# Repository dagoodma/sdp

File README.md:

.oo          o                                                   
        .P 8          8                                                   
       .P  8 o    o  o8P .oPYo. odYo. .oPYo. ooYoYo. .oPYo. o    o .oPYo. 
      oPooo8 8    8   8  8    8 8' `8 8    8 8' 8  8 8    8 8    8 Yb..   
     .P    8 8    8   8  8    8 8   8 8    8 8  8  8 8    8 8    8   'Yb. 
    .P     8 `YooP'   8  `YooP' 8   8 `YooP' 8  8  8 `YooP' `YooP' `YooP' 
    ..:::::..:.....:::..::.....:..::..:.....:..:..:..:.....::.....::.....:
    ::::::::::::::::::::::::::::::::::::::::::::::::::::::::::::::::::::::
    ::::::::::::::::::::::::::::::::::::::::::::::::::::::::::::::::::::::
    
           o      o  d'b                                        8 
           8         8                                          8 
           8     o8 o8P  .oPYo. .oPYo. o    o .oPYo. oPYo. .oPYo8 
           8      8  8   8oooo8 8    8 8    8 .oooo8 8  `' 8    8 
           8      8  8   8.     8    8 8    8 8    8 8     8    8 
           8oooo  8  8   `Yooo' `YooP8 `YooP' `YooP8 8     `YooP' 
     ............:..:..:::.....::....8 :.....::.....:..:::::.....::.....::.
    ::::::::::::::::::::::::::::::ooP'.:::::::::::::::::::::::::::::::::::
    ::::::::::::::::::::::::::::::...:::::::::::::::::::::::::::::::::::'

Autonomous Lifeguard -- Senior Design Project for UCSC

*   Website: http://lifeguardrobotics.com
*   Source: https://github.com/dagoodma/sdp
*   Mailing list: [Google Groups](https://groups.google.com/a/ucsc.edu/forum/#!forum/albs-group)

This project consists of an autonomous surface vessel to aid a drowning
individual in the critical minutes that it takes a lifeguard to make it
out to a person. 

### License ###

The Autonomous Lifeguard project is proposed to be protected under either LGPL or GPLv3+.
See the *COPYING* file for more info.

### Credits ###

&copy; 2012-2013 [David Goodman](mailto:dagoodma@ucsc.edu),
 [Darrel Deo](mailto:ddeo@ucsc.edu),
 [Shehadeh Dajani](mailto:sdajani@ucsc.edu),
 [John Ash](mailto:jash@ucsc.edu)

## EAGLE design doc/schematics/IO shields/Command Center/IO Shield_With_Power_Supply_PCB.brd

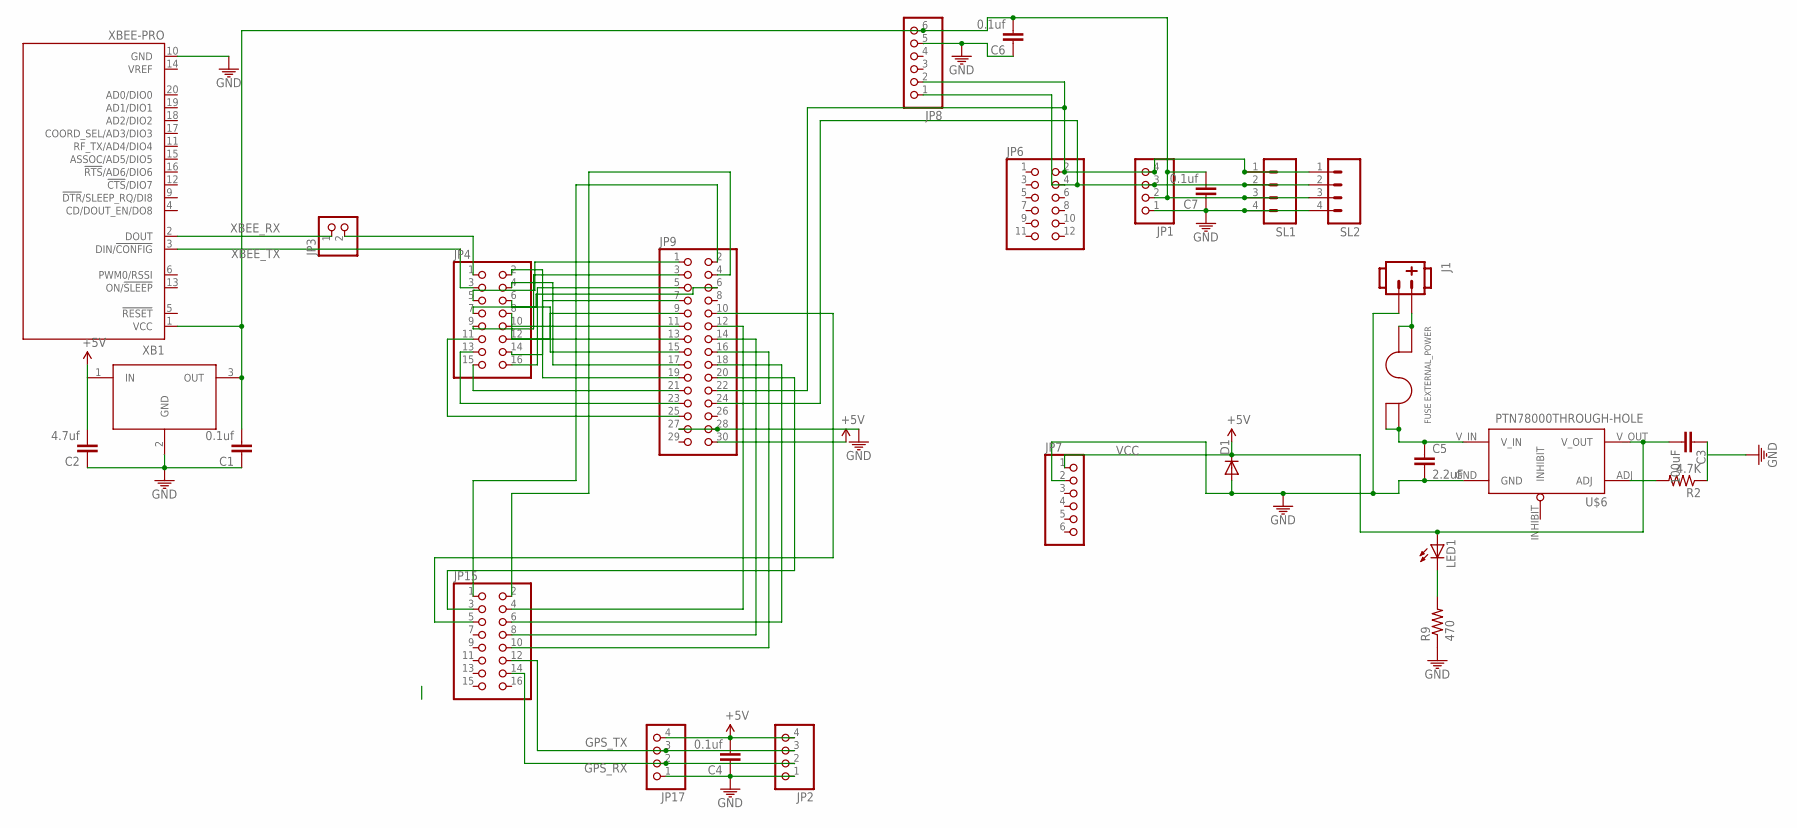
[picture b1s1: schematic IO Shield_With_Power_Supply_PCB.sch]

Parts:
C1, C4, C6, C7: 0.1uf; C0805
C2: 4.7uf; C0805
C3: 100uF; C0805
C5: 2.2uF; C0805
D1: DIODEPTH; DIODE-1N4001
EXTERNAL_POWER: FUSE; FUSE_2AG
J1: POW_CONNECTMALE; SOCKET-MALE-3.96MM-2
JP1, JP17: PINHD-1X4; 1X04
JP2: PINHD-1X4/90; 1X04/90
JP3: PINHD-1X2; 1X02
JP4, JP15: PINHD-2X8; 2X08
JP6: PINHD-2X6; 2X06
JP7, JP8: PINHD-1X6; 1X06
JP9: PINHD-2X15/90; 2X15/90
LED1: LED-FKIT-1206; FKIT-LED-1206
R2: 4.7K; 0805
R9: 470; 0805
SL1, SL2: M04LOCK; 1X04_LOCK
U$6: PTN78000THROUGH-HOLE; PTN78000
U$7: LM3940IMP-3.3; SOT223
XB1: XBEE-PRO

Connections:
GND: C1.1, C2.1, C3.1, C4.1, C5.2, C6.1, C7.1, D1.A, J1.P$2 (2), JP1.1, JP2.1, JP7.2, JP8.5, JP9.27, JP9.28, JP17.1, R2.1, R9.1, SL1.4, SL2.4, U$6.GND, U$7.2 (GND), XB1.10 (GND)
GPS_RX: JP2.2, JP15.14, JP17.2
GPS_TX: JP2.3, JP15.12, JP17.3
unnamed: JP3.1, XB1.2 (DOUT)
unnamed: JP4.5, JP9.1
unnamed: EXTERNAL_POWER.P$1 (1), EXTERNAL_POWER.P$2 (2), J1.P$1 (1)
unnamed: JP4.9, JP9.3
unnamed: JP4.7, JP9.6
unnamed: JP9.2, JP15.1
unnamed: JP9.4, JP15.2
unnamed: JP4.16, JP9.5
unnamed: JP4.14, JP9.7
unnamed: JP4.12, JP9.9
unnamed: JP9.10, JP15.5
unnamed: JP4.10, JP9.11
unnamed: C1.2, C6.2, C7.2, JP1.2, JP8.6, SL1.3, SL2.3, U$7.3 (OUT), XB1.1 (VCC)
unnamed: JP4.8, JP9.13
unnamed: C5.1, EXTERNAL_POWER.P$3 (3), EXTERNAL_POWER.P$4 (4), U$6.V_IN
unnamed: JP4.6, JP9.15
unnamed: JP4.4, JP9.17
unnamed: JP4.2, JP9.19
unnamed: JP4.15, JP9.21
unnamed: JP4.13, JP9.23
unnamed: JP4.11, JP9.25
unnamed: JP9.14, JP15.8
unnamed: JP9.18, JP15.6
unnamed: LED1.C, R9.2
unnamed: JP1.4, JP6.2, JP8.2, JP9.22, SL1.1, SL2.1
unnamed: JP9.16, JP15.10
unnamed: JP9.12, JP15.4
unnamed: JP9.20, JP15.3
unnamed: R2.2, U$6.ADJ
unnamed: JP1.3, JP6.4, JP8.1, JP9.24, SL1.2, SL2.2
VCC: C2.2, C3.2, C4.2, D1.C, JP2.4, JP7.1, JP9.30, JP17.4, LED1.A, U$6.V_OUT, U$7.1 (IN)
XBEE_RX: JP3.2, JP4.1
XBEE_TX: JP4.3, XB1.3 (DIN/!CONFIG)

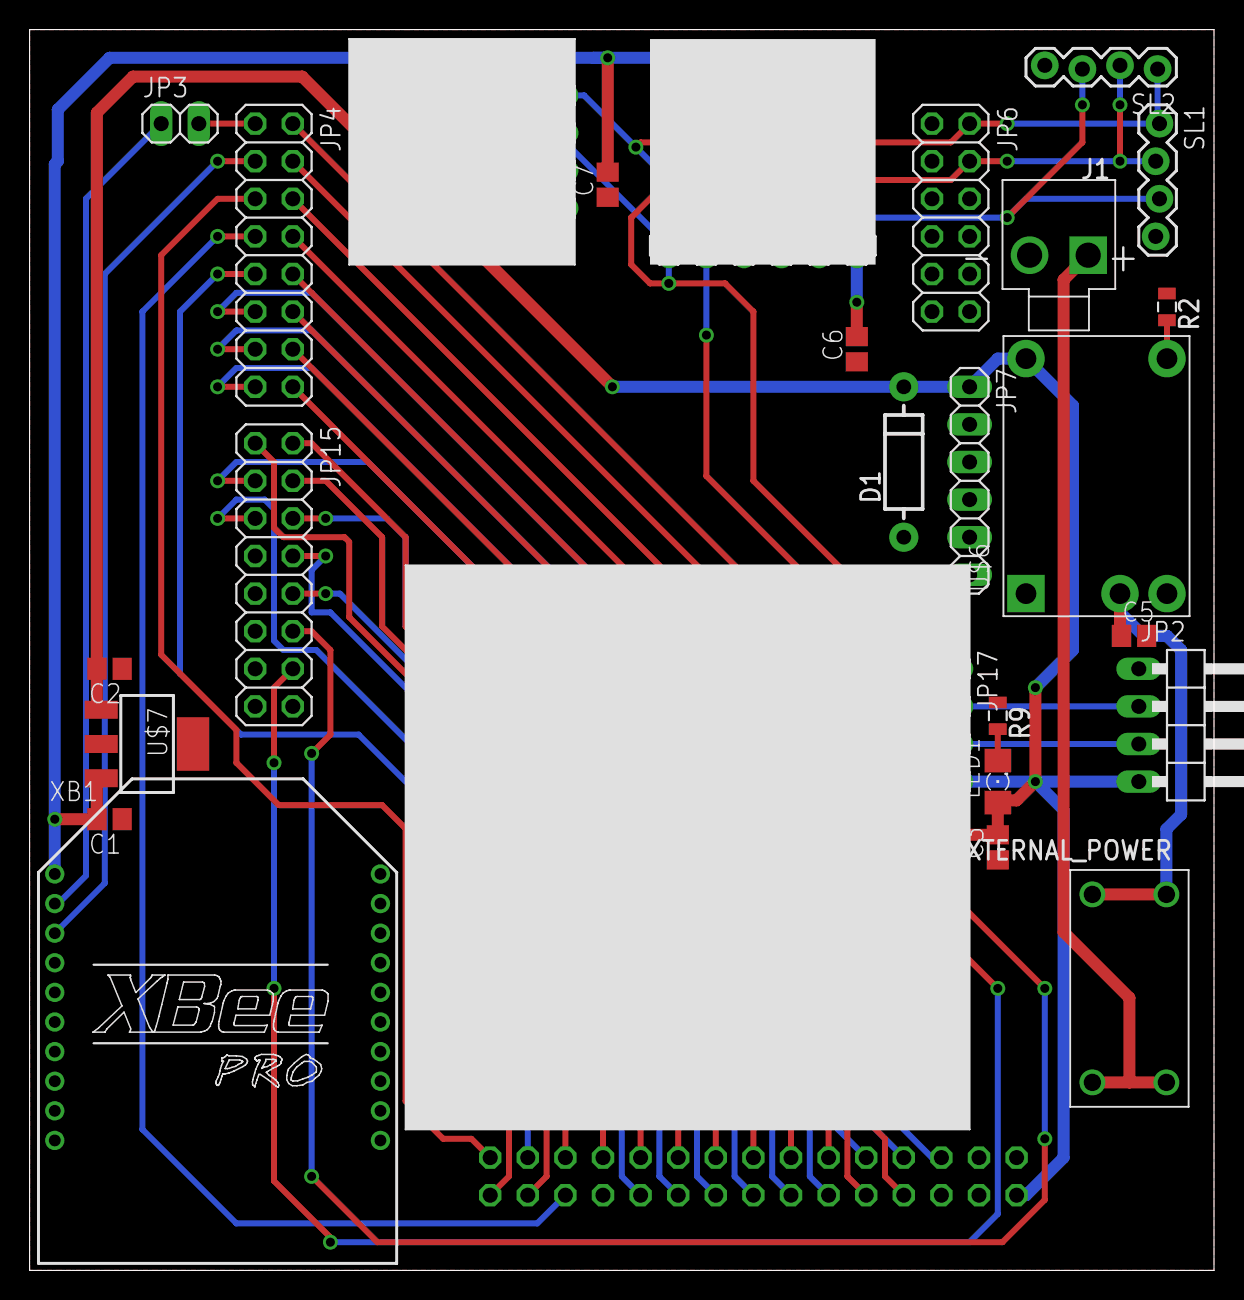
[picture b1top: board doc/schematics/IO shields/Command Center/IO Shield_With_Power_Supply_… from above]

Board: 2 copper layers, 80.0 x 83.8 mm, 32 parts (1 on the bottom side), 36 nets.

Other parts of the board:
U$2, U$3, U$4, U$5: STAND-OFF

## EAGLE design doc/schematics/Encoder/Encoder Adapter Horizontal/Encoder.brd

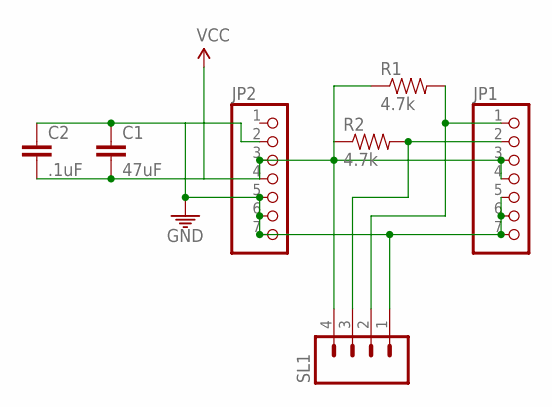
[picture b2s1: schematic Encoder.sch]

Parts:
C1: 47uF; 0805
C2: .1uF; 0805
JP1, JP2: PINHD-1X7; 1X07
R1, R2: 4.7k; 0805
SL1: M04LOCK; 1X04_LOCK

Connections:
GND: C1.1, C2.1, JP1.5, JP1.6, JP1.7, JP2.2, JP2.5, JP2.6, JP2.7, SL1.1
unnamed: JP1.1, R1.2, SL1.2
unnamed: JP1.2, R2.2, SL1.3
VCC: C1.2, C2.2, JP1.3, JP1.4, JP2.3, JP2.4, R1.1, R2.1, SL1.4

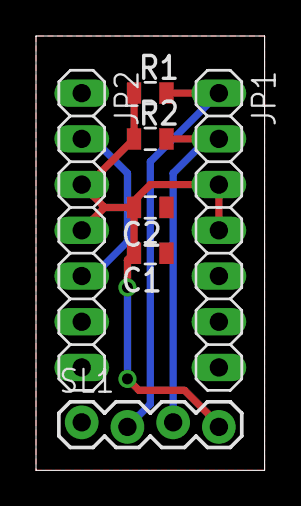
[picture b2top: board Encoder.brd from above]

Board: 2 copper layers, 12.7 x 24.1 mm, 7 parts (0 on the bottom side), 4 nets.

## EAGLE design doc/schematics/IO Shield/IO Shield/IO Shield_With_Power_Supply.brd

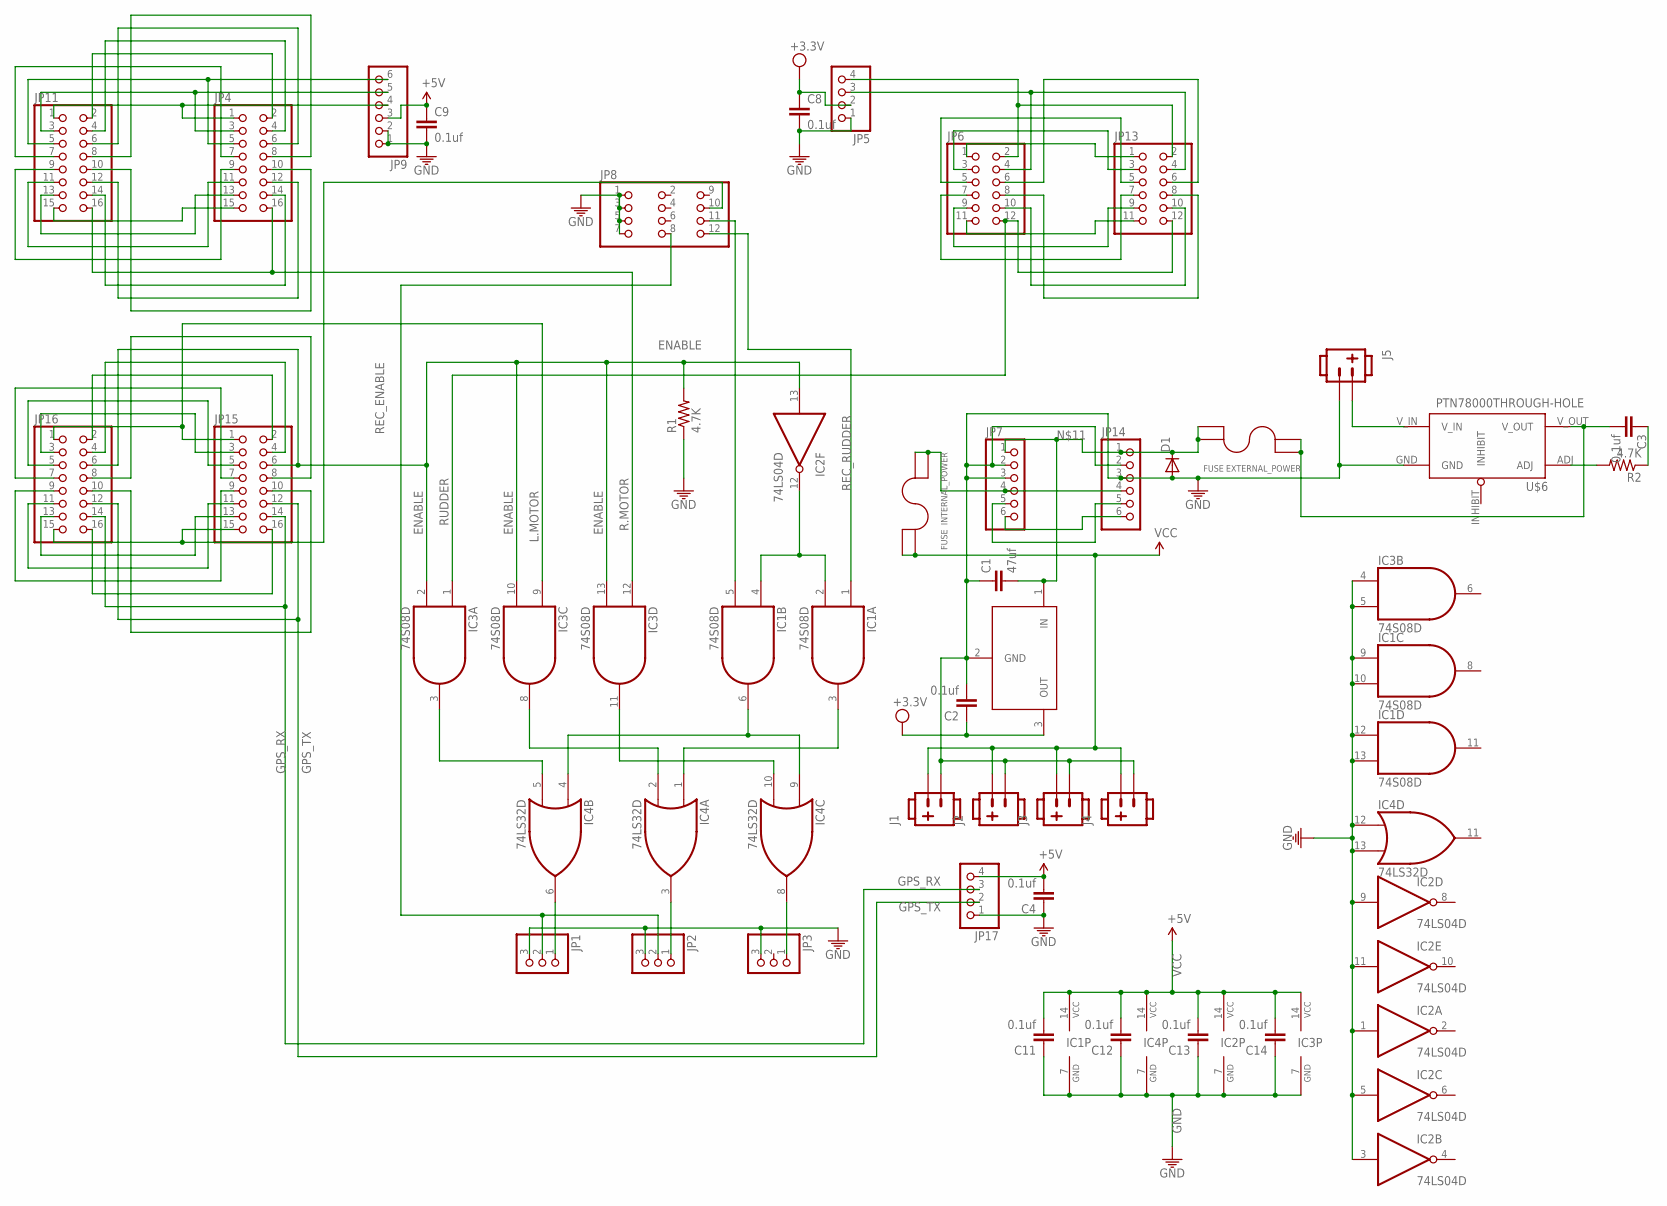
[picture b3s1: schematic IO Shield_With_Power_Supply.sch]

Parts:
C1: 47uf; C0805
C2, C3, C4, C8, C9, C11, C12, C13, C14: 0.1uf; C0805
D1: DIODEPTH; DIODE-1N4001
EXTERNAL_POWER: FUSE; FUSE_2AG
IC1, IC3: 74S08D; SO14
IC2: 74LS04D; SO14
IC4: 74LS32D; SO14
INTERNAL_POWER: FUSE; FUSE_2AG
J1, J2, J3, J4, J5: POW_CONNECTFEMALE-RA; SOCKET-FEMALE_RA-3.96MM-2
JP1, JP2, JP3: PINHD-1X3/90; 1X03/90
JP4, JP11, JP15, JP16: PINHD-2X8; 2X08
JP5, JP17: PINHD-1X4; 1X04
JP6, JP13: PINHD-2X6; 2X06
JP7, JP9, JP14: PINHD-1X6; 1X06
JP8: PINHD-2X4; 2X04
R1, R2: 4.7K; 0805
U$1: LM3940IMP-3.3; SOT223
U$6: PTN78000THROUGH-HOLE; PTN78000

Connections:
ENABLE: IC2.13 (I), IC3.2 (I1), IC3.10 (I1), IC3.13 (I1), JP15.6, JP16.6, R1.2
GND: C1.1, C2.2, C4.1, C8.2, C9.2, C11.1, C12.1, C13.1, C14.1, D1.A, IC1.7 (GND), IC1.9 (I0), IC1.10 (I1), IC1.12 (I0), IC1.13 (I1), IC2.1 (I), IC2.3 (I), IC2.5 (I), IC2.7 (GND), IC2.9 (I), IC2.11 (I), IC3.4 (I0), IC3.5 (I1), IC3.7 (GND), IC4.7 (GND), IC4.12 (I0), IC4.13 (I1), J1.2, J2.2, J3.2, J4.2, J5.2, JP1.3, JP2.3, JP3.3, JP5.1, JP7.2, JP7.3, JP8.1, JP8.3, JP8.5, JP8.7, JP9.1, JP9.2, JP14.2, JP14.3, JP17.1, R1.1, U$1.2 (GND), U$6.GND
GPS_RX: JP15.14, JP16.14, JP17.3
GPS_TX: JP15.12, JP16.12, JP17.2
L.MOTOR: IC3.9 (I0), JP15.1, JP16.1
unnamed: IC1.3 (O), IC4.1 (I0)
unnamed: IC1.6 (O), IC4.4 (I0), IC4.9 (I0)
unnamed: IC1.2 (I1), IC1.4 (I0), IC2.12 (O)
unnamed: JP4.1, JP9.4, JP11.1
unnamed: IC3.11 (O), IC4.10 (I1)
unnamed: IC3.8 (O), IC4.2 (I1)
unnamed: IC3.3 (O), IC4.5 (I1)
unnamed: IC4.6 (O), JP1.1
unnamed: IC4.3 (O), JP2.1
unnamed: IC4.8 (O), JP3.1
unnamed: C1.2, D1.C, EXTERNAL_POWER.P$3 (3), EXTERNAL_POWER.P$4 (4), JP7.1, JP14.1, U$1.1 (IN)
unnamed: JP1.2, JP2.2, JP8.8
unnamed: C3.2, EXTERNAL_POWER.P$1 (1), EXTERNAL_POWER.P$2 (2), U$6.V_OUT
unnamed: JP8.10 (9), JP15.15, JP16.15
unnamed: JP6.1, JP13.1
unnamed: J5.1, U$6.V_IN
unnamed: JP4.3, JP9.5, JP11.3
unnamed: JP4.5, JP9.6, JP11.5
unnamed: JP4.7, JP11.7
unnamed: JP4.15, JP11.15
unnamed: JP4.13, JP11.13
unnamed: JP4.11, JP11.11
unnamed: JP4.9, JP11.9
unnamed: JP4.2, JP11.2
unnamed: JP4.4, JP11.4
unnamed: JP4.6, JP11.6
unnamed: JP4.8, JP11.8
unnamed: JP4.14, JP11.14
unnamed: JP4.12, JP11.12
unnamed: JP4.10, JP11.10
unnamed: JP6.3, JP13.3
unnamed: JP15.3, JP16.3
unnamed: JP15.5, JP16.5
unnamed: JP15.7, JP16.7
unnamed: R2.2, U$6.ADJ
unnamed: JP15.13, JP16.13
unnamed: JP15.11, JP16.11
unnamed: JP15.9, JP16.9
unnamed: JP15.2, JP16.2
unnamed: JP15.4, JP16.4
unnamed: JP6.5, JP13.5
unnamed: JP15.8, JP16.8
unnamed: C3.1, R2.1
unnamed: INTERNAL_POWER.P$1 (1), INTERNAL_POWER.P$2 (2), JP7.4, JP14.4
unnamed: JP15.10, JP16.10
unnamed: JP6.7, JP13.7
unnamed: JP6.9, JP13.9
unnamed: JP6.11, JP13.11
unnamed: JP5.4, JP6.2, JP13.2
unnamed: JP5.3, JP6.4, JP13.4
unnamed: JP6.6, JP13.6
unnamed: JP6.8, JP13.8
unnamed: JP6.10, JP13.10
unnamed: JP7.5, JP14.5
unnamed: JP7.6, JP14.6
R.MOTOR: IC3.12 (I0), JP4.16, JP11.16
REC.MOTOR: IC1.5 (I1), JP8.11
REC_ENABLE: JP15.16, JP16.16
REC_RUDDER: IC1.1 (I0), JP8.12
RUDDER: IC3.1 (I0), JP6.12, JP13.12
VCC: C4.2, C9.1, C11.2, C12.2, C13.2, C14.2, IC1.14 (VCC), IC2.14 (VCC), IC3.14 (VCC), IC4.14 (VCC), INTERNAL_POWER.P$3 (3), INTERNAL_POWER.P$4 (4), J1.1, J2.1, J3.1, J4.1, JP9.3, JP17.4
VDD: C2.1, C8.1, JP5.2, U$1.3 (OUT)

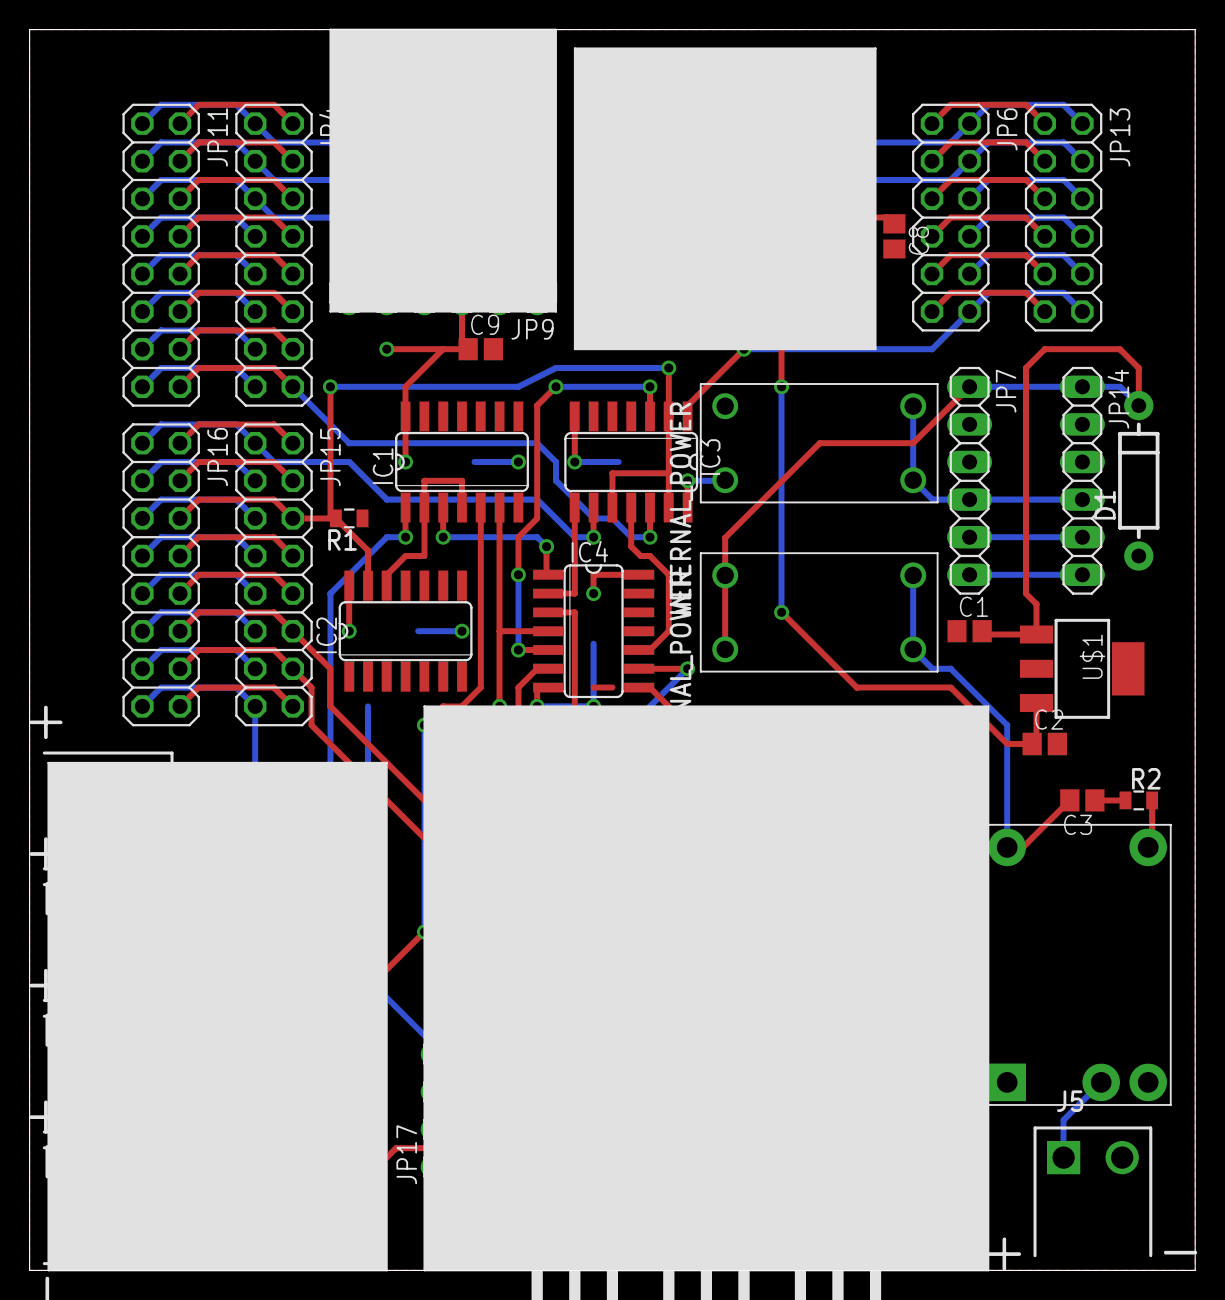
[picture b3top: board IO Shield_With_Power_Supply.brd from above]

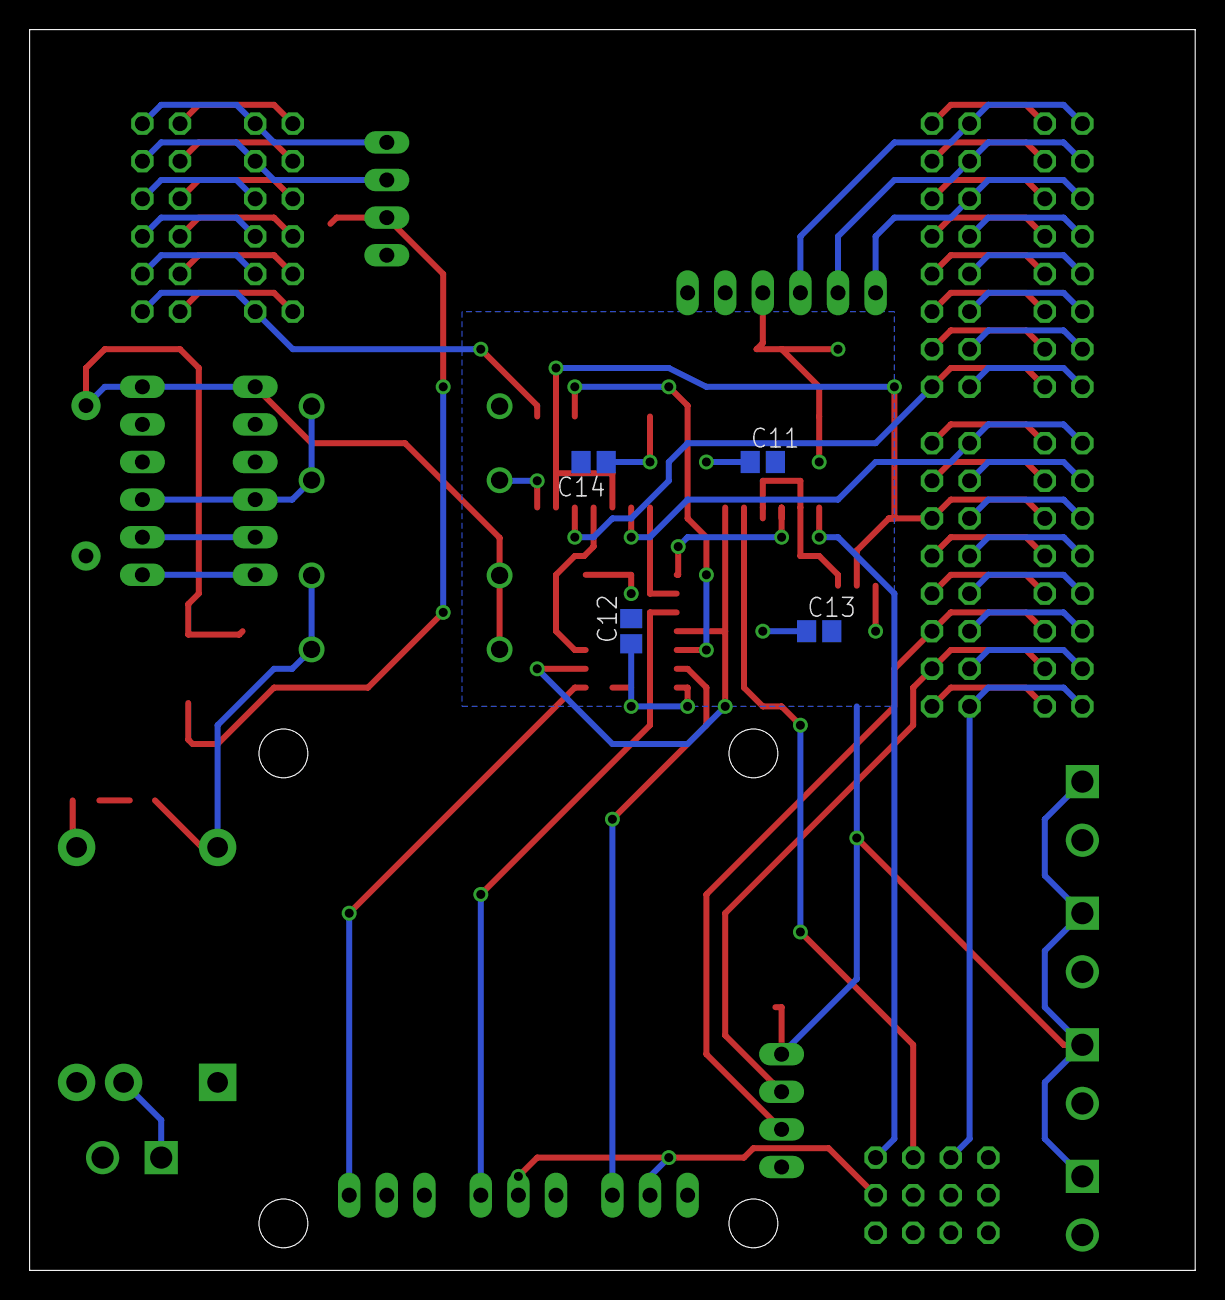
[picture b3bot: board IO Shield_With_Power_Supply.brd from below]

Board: 2 copper layers, 78.7 x 83.8 mm, 45 parts (4 on the bottom side), 67 nets.

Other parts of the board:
U$2, U$3, U$4, U$5: STAND-OFF

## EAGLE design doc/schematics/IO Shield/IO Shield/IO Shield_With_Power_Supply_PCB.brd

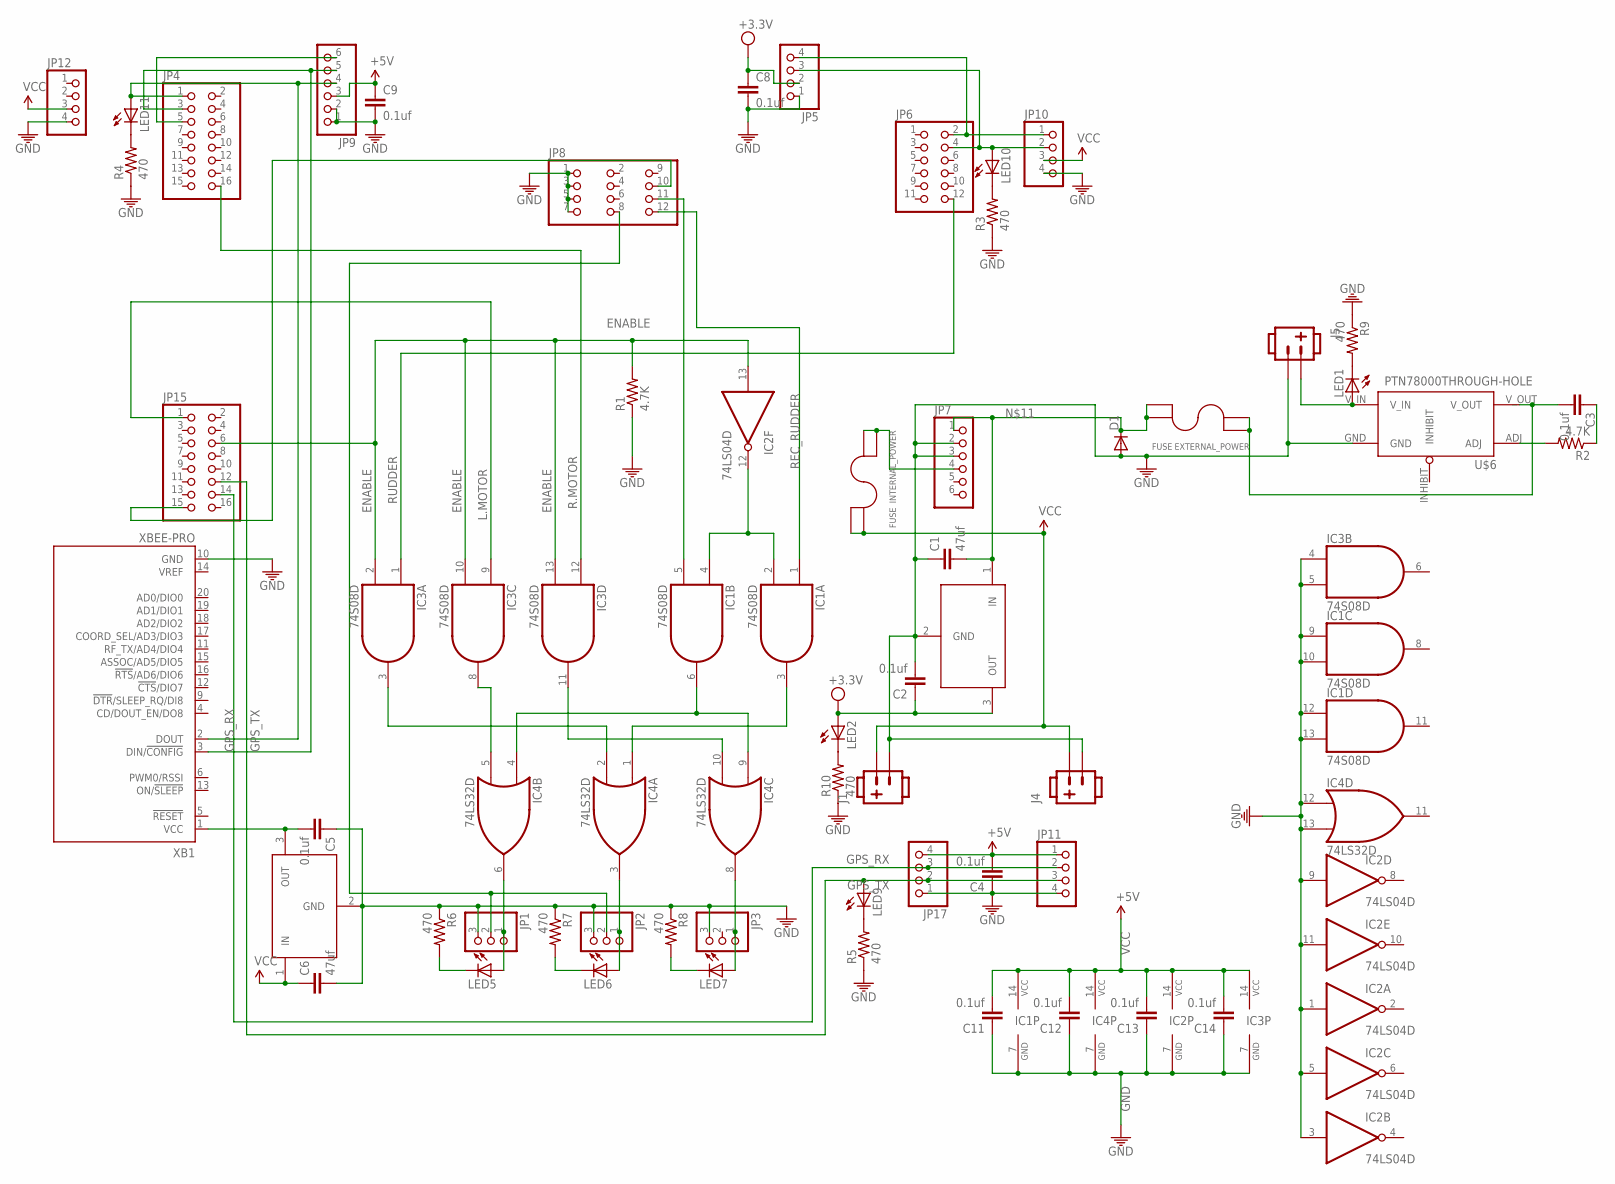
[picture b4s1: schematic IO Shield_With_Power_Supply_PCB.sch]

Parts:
C1, C6: 47uf; C0805
C2, C3, C4, C5, C8, C9, C11, C12, C13, C14: 0.1uf; C0805
D1: DIODEPTH; DIODE-1N4001
EXTERNAL_POWER: FUSE; FUSE_2AG
IC1, IC3: 74S08D; SO14
IC2: 74LS04D; SO14
IC4: 74LS32D; SO14
INTERNAL_POWER: FUSE; FUSE_2AG
J1, J4, J5: POW_CONNECTFEMALE-RA; SOCKET-FEMALE_RA-3.96MM-2
JP1, JP2, JP3: PINHD-1X3/90; 1X03/90
JP4, JP15: PINHD-2X8; 2X08
JP5, JP17: PINHD-1X4; 1X04
JP6: PINHD-2X6; 2X06
JP7, JP9: PINHD-1X6; 1X06
JP8: PINHD-2X4; 2X04
JP10, JP11, JP12: PINHD-1X4/90; 1X04/90
LED1, LED2, LED5, LED6, LED7, LED9, LED10, LED11: LED-FKIT-1206; FKIT-LED-1206
R1, R2: 4.7K; 0805
R3, R4, R5, R6, R7, R8, R9, R10: 470; 0805
U$1, U$7: LM3940IMP-3.3; SOT223
U$6: PTN78000THROUGH-HOLE; PTN78000
XB1: XBEE-PRO

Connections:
ENABLE: IC2.13 (I), IC3.2 (I1), IC3.10 (I1), IC3.13 (I1), JP15.6, R1.2
GND: C1.1, C2.2, C4.1, C5.1, C6.2, C8.2, C9.2, C11.1, C12.1, C13.1, C14.1, D1.A, IC1.7 (GND), IC1.9 (I0), IC1.10 (I1), IC1.12 (I0), IC1.13 (I1), IC2.1 (I), IC2.3 (I), IC2.5 (I), IC2.7 (GND), IC2.9 (I), IC2.11 (I), IC3.4 (I0), IC3.5 (I1), IC3.7 (GND), IC4.7 (GND), IC4.12 (I0), IC4.13 (I1), J1.2, J4.2, J5.2, JP1.3, JP2.3, JP3.3, JP5.1, JP7.2, JP7.3, JP8.1, JP8.3, JP8.5, JP8.7, JP9.1, JP9.2, JP10.4, JP11.4, JP12.4, JP17.1, R1.1, R3.1, R4.1, R5.1, R6.1, R7.1, R8.1, R9.1, R10.1, U$1.2 (GND), U$6.GND, U$7.2 (GND), XB1.10 (GND)
GPS_RX: JP11.2, JP15.14, JP17.3
GPS_TX: JP11.3, JP15.12, JP17.2, LED9.A
L.MOTOR: IC3.9 (I0), JP15.1
unnamed: IC1.3 (O), IC4.1 (I0)
unnamed: IC1.6 (O), IC4.4 (I0), IC4.9 (I0)
unnamed: IC1.2 (I1), IC1.4 (I0), IC2.12 (O)
unnamed: JP4.1, JP9.4, LED11.A, XB1.2 (DOUT)
unnamed: IC3.11 (O), IC4.10 (I1)
unnamed: IC3.8 (O), IC4.5 (I1)
unnamed: IC4.6 (O), JP1.1, LED5.A
unnamed: IC4.3 (O), JP2.1, LED6.A
unnamed: IC4.8 (O), JP3.1, LED7.A
unnamed: C1.2, D1.C, EXTERNAL_POWER.P$3 (3), EXTERNAL_POWER.P$4 (4), JP7.1, U$1.1 (IN)
unnamed: JP1.2, JP2.2, JP8.8
unnamed: C3.2, EXTERNAL_POWER.P$1 (1), EXTERNAL_POWER.P$2 (2), U$6.V_OUT
unnamed: JP8.10 (9), JP15.15
unnamed: C5.2, U$7.3 (OUT), XB1.1 (VCC)
unnamed: J5.1, LED1.A, U$6.V_IN
unnamed: JP4.3, JP9.5, XB1.3 (DIN/!CONFIG)
unnamed: JP4.5, JP9.6
unnamed: LED10.C, R3.2
unnamed: LED11.C, R4.2
unnamed: LED9.C, R5.2
unnamed: LED5.C, R6.2
unnamed: LED6.C, R7.2
unnamed: LED7.C, R8.2
unnamed: LED1.C, R9.2
unnamed: LED2.C, R10.2
unnamed: IC3.3 (O), IC4.2 (I1)
unnamed: R2.2, U$6.ADJ
unnamed: C3.1, R2.1
unnamed: INTERNAL_POWER.P$1 (1), INTERNAL_POWER.P$2 (2), JP7.4
unnamed: JP5.4, JP6.2, JP10.1
unnamed: JP5.3, JP6.4, JP10.2, LED10.A
R.MOTOR: IC3.12 (I0), JP4.16
REC.MOTOR: IC1.5 (I1), JP8.11
REC_RUDDER: IC1.1 (I0), JP8.12
RUDDER: IC3.1 (I0), JP6.12
VCC: C4.2, C6.1, C9.1, C11.2, C12.2, C13.2, C14.2, IC1.14 (VCC), IC2.14 (VCC), IC3.14 (VCC), IC4.14 (VCC), INTERNAL_POWER.P$3 (3), INTERNAL_POWER.P$4 (4), J1.1, J4.1, JP9.3, JP10.3, JP11.1, JP12.3, JP17.4, U$7.1 (IN)
VDD: C2.1, C8.1, JP5.2, LED2.A, U$1.3 (OUT)

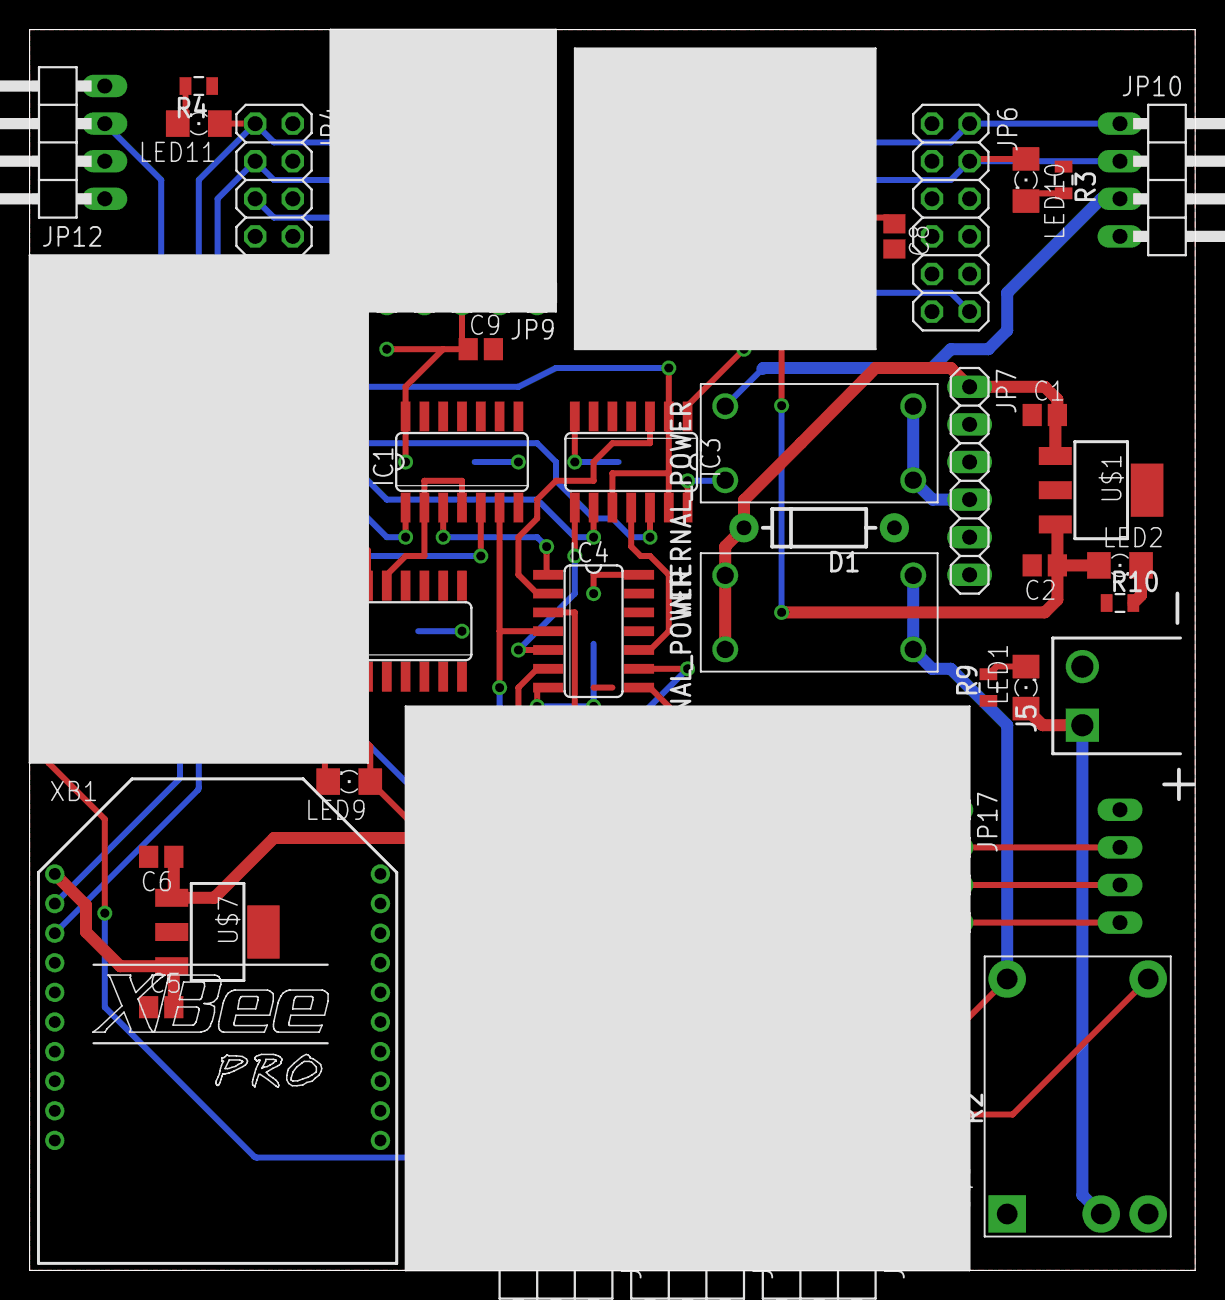
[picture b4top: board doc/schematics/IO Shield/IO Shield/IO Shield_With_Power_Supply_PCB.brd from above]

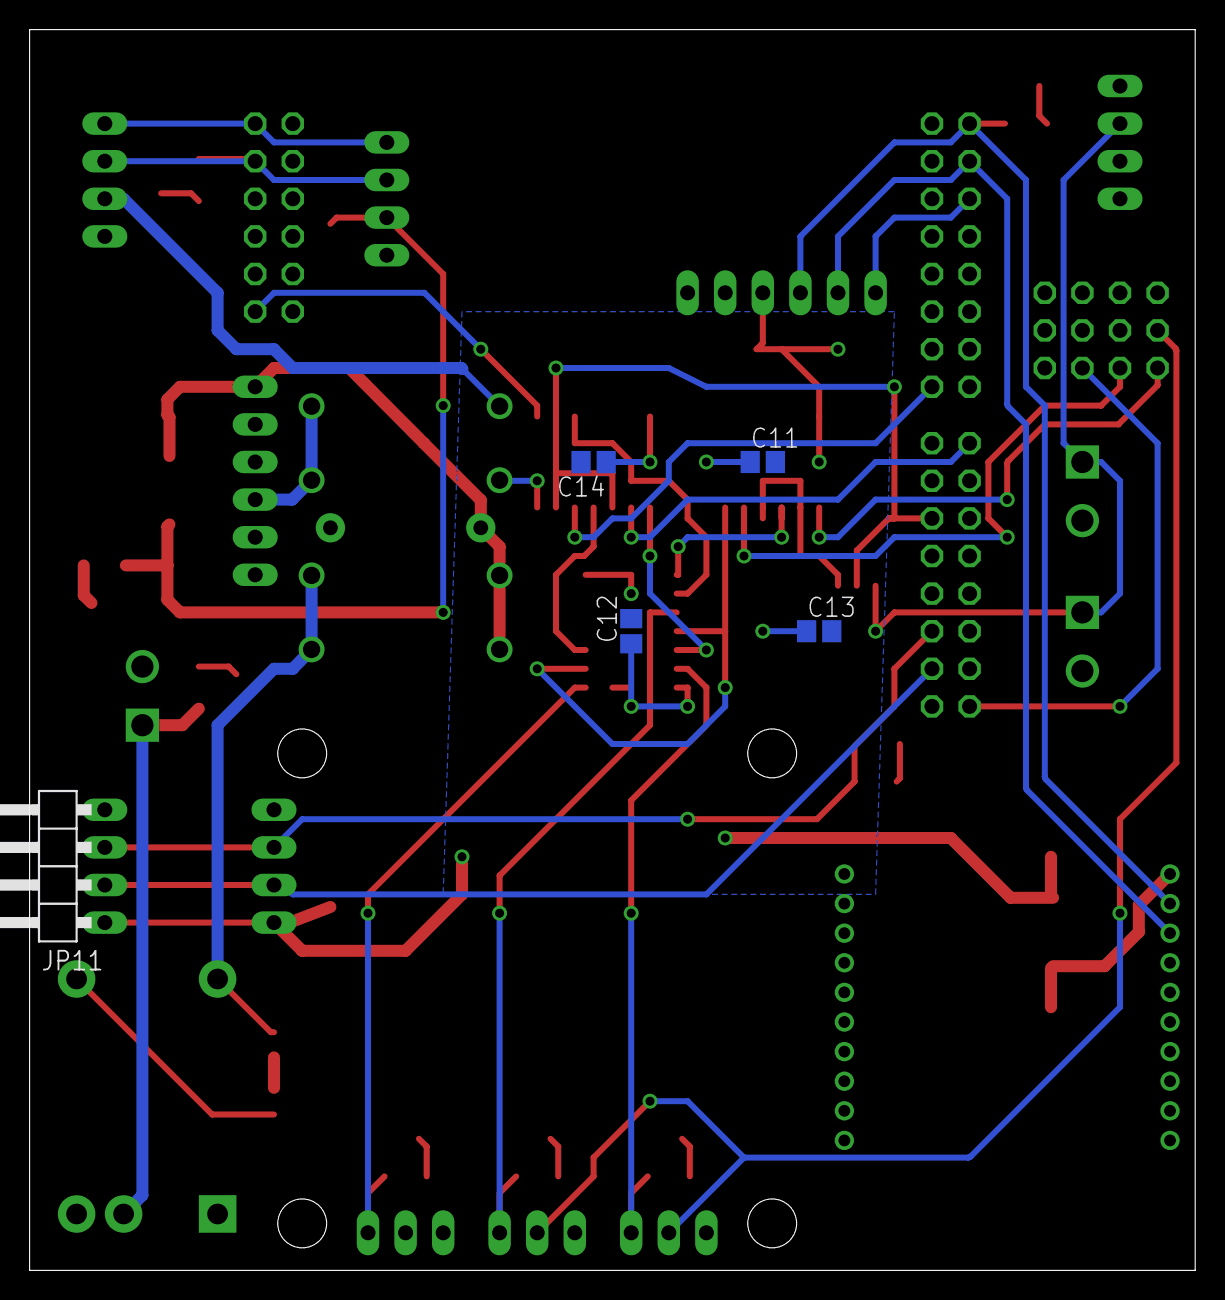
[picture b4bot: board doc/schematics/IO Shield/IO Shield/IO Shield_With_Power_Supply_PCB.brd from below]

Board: 2 copper layers, 78.7 x 83.8 mm, 62 parts (5 on the bottom side), 42 nets.

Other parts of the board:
U$2, U$3, U$4, U$5: STAND-OFF

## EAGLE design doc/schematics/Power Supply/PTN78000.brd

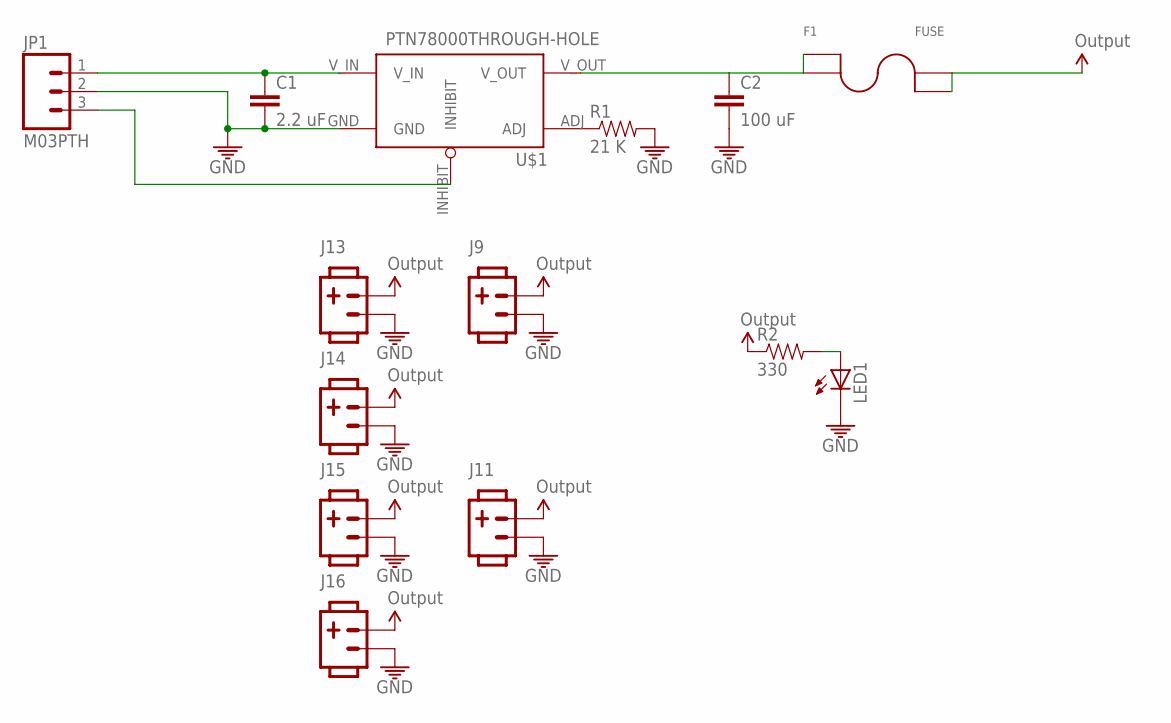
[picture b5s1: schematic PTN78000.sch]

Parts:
C1: 2.2 uF; 1206
C2: 100 uF; 1206
F1: FUSE; FUSE_2AG
J9, J11, J13, J14, J15, J16: POW_CONNECTFEMALE-RA; SOCKET-FEMALE_RA-3.96MM-2
JP1: M03PTH; 1X03
LED1: LED5MM
R1: 21 K; 1206
R2: 330; 1206
U$1: PTN78000THROUGH-HOLE; PTN78000

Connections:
GND: C1.2, C2.2, J9.2, J11.2, J13.2, J14.2, J15.2, J16.2, JP1.2, LED1.K (C), R1.2, U$1.GND
unnamed: C1.1, JP1.1, U$1.V_IN
unnamed: R1.1, U$1.ADJ
unnamed: JP1.3, U$1.INHIBIT
unnamed: C2.1, F1.P$1 (1), F1.P$2 (2), U$1.V_OUT
unnamed: LED1.A, R2.2
VCC5V0: F1.P$3 (3), F1.P$4 (4), J9.1, J11.1, J13.1, J14.1, J15.1, J16.1, R2.1

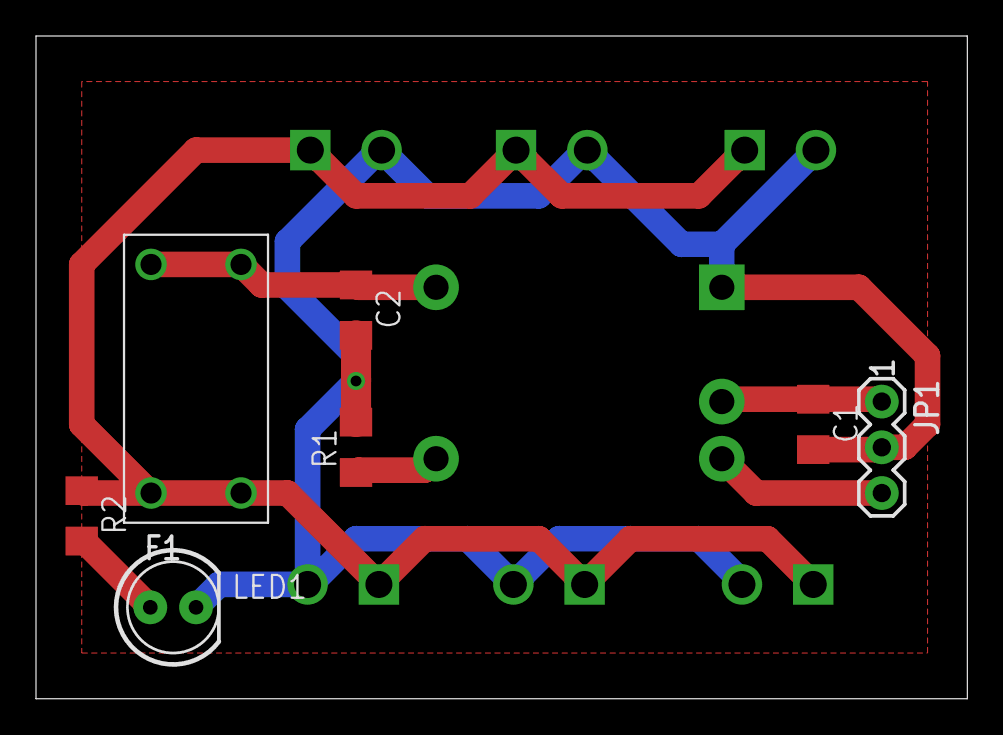
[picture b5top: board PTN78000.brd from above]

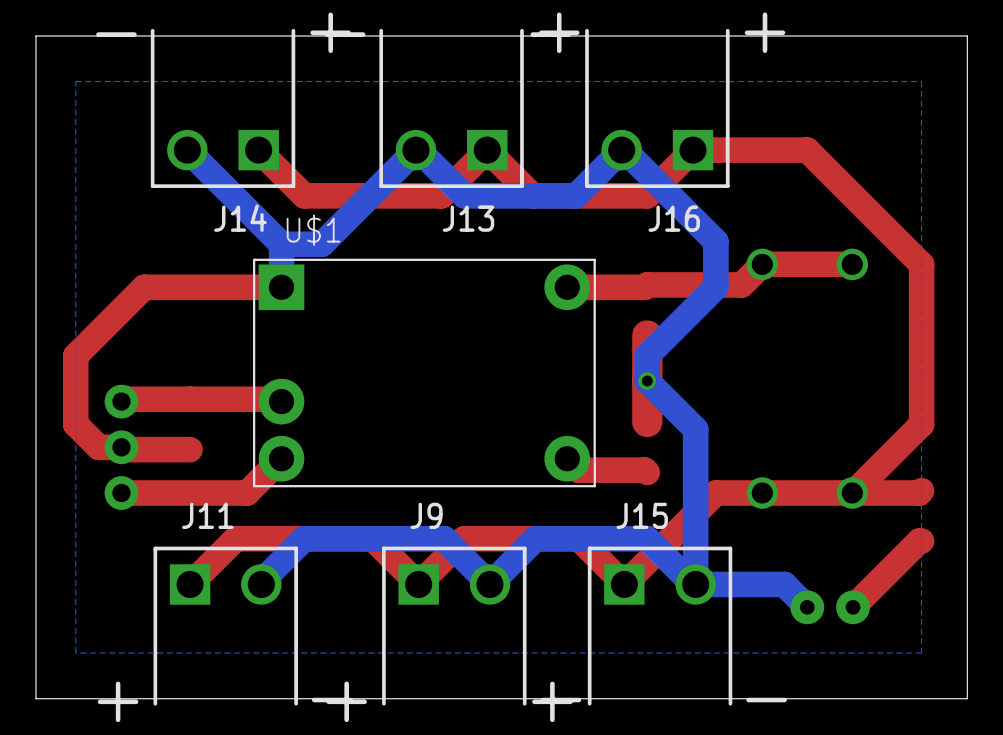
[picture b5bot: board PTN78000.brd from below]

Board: 2 copper layers, 51.7 x 36.8 mm, 14 parts (7 on the bottom side), 7 nets.

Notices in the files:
parts and their libraries:
SparkFun-Connectors: Licensing: CC v3.0 Share-Alike You are welcome to use this library for commercial purposes.
SparkFun-Aesthetics: Released under the Creative Commons Attribution Share-Alike 3.0 License
SparkFun-Aesthetics: http://creativecommons.org/licenses/by-sa/3.0
